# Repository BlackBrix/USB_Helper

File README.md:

# USB_Helper
### A USB switch that enables you to switch the 4 lines (data and power) individually ON or OFF
----
A very useful device not only for makers.  
The four lines 5V,GND,D+,D- can be individually switched ON or OFF (connected or disconnected).  
Look at the pictures, it's pretty self-explanatory...  

### Usecase 1:
Charging (or power supplying) a device (e.g. your mobile / mp3-player / camera) with an "unknown" PC or your companies PC.  
You don't know if this PC "scans" all your private and confidential data,  
you don't know if this PC is "infected" with some virus or malware !  
**Simply switch off the 2 data-lines (D+ and D-) on the USB-Helper and you are protected.**  

### Usecase 2:
Sometimes you want to communicate with a device but without connecting the 5V from the PC.  
(quite often the 5V-supply from a PC is very noisy, with voltage spikes or some humming occurs...)  
**examples:**  
 -- communicating with a microcontroller system that has it's own power supply (3.3V / or own 5V-System)  
 -- using USB audio systems (e.g. external D/A-converter) with own power supply without "injecting" noises and humming from the PC.  
**Simply switch off the 5V-line on the USB-Helper and you are ready to go.**  
(in some scenarios even the GND switch can be disconnected as well, you have to try)  

### Specifications:
* the four lines 5V,GND,D+,D- can be individually switched ON or OFF (connected or disconnected)
* USB "Type A" male and female connector
* compatible with USB 1.0 / USB 2.0 devices
* compatible with Low Speed [1,5 Mbit/s], Full Speed [12 Mbit/s], Hi-Speed [480 Mbit/s] devices
* the (special heavy-duty) DIP-switch is capable of switching and holding a load of 500mA
* a transparent heat shrink tube is used as protection against short circuit
* dimensions assembled: 50,9mm x 16,6mm x 12,5mm (length x width x height)
* dimensions bare PCB only: 30,1mm x 16,6mm x 1,7mm (length x width x height)  
  
----

get one ->  

----

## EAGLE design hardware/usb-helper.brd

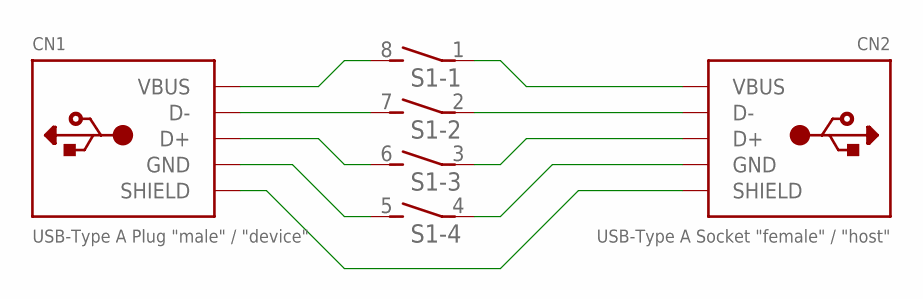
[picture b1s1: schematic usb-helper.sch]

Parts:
CN1: USB-Type A Plug "male" / "device"; USB_PLUG_A_THT_AWF
CN2: USB-Type A Socket "female" / "host"; USB_SOCKET_A_THT_AW
S1: DIP04S_SECME; DIP_04_SECME_THT

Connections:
D+: CN1.D+, S1.6 (2)
D+_S: CN2.D+, S1.3 (1)
D-: CN1.D-, S1.7 (2)
D-_S: CN2.D-, S1.2 (1)
GND: CN1.GND, S1.5 (2)
GND_S: CN2.GND, S1.4 (1)
SHIELD: CN1.SHIELD1 (SHIELD), CN1.SHIELD2 (SHIELD), CN2.S1 (SHIELD), CN2.S2 (SHIELD)
VBUS: CN1.VBUS, S1.8 (2)
VBUS_S: CN2.VBUS, S1.1

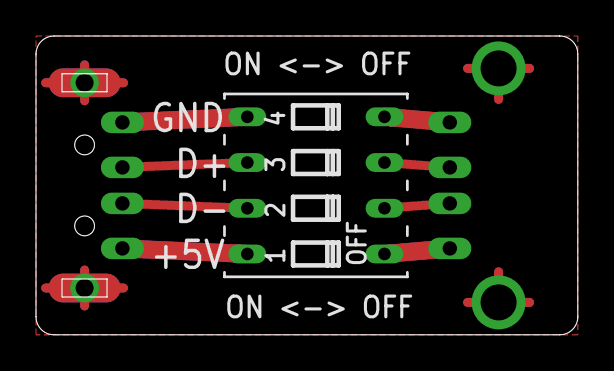
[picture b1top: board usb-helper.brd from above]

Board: 2 copper layers, 30.1 x 16.6 mm, 3 parts (0 on the bottom side), 9 nets.

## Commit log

2016-02-26 Create test
2016-02-26 Added files via upload
2016-04-13 Rename enclosure/test to readme.md
2017-11-21 Rename enclosure/usb-helper-v2-x1.gcode to enclosure V1/usb-helper-v2-x1.gcode

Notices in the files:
parts and their libraries:
microbuilder: This work is placed in the public domain, and may be freely used for commercial and non-commercial work with the following conditions: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
